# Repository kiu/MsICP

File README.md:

# MsICP

Animated LED sign

# License

This project is licensed under the Creative Commons Attribution-NonCommercial 3.0 Unported (CC BY-NC 3.0) license.

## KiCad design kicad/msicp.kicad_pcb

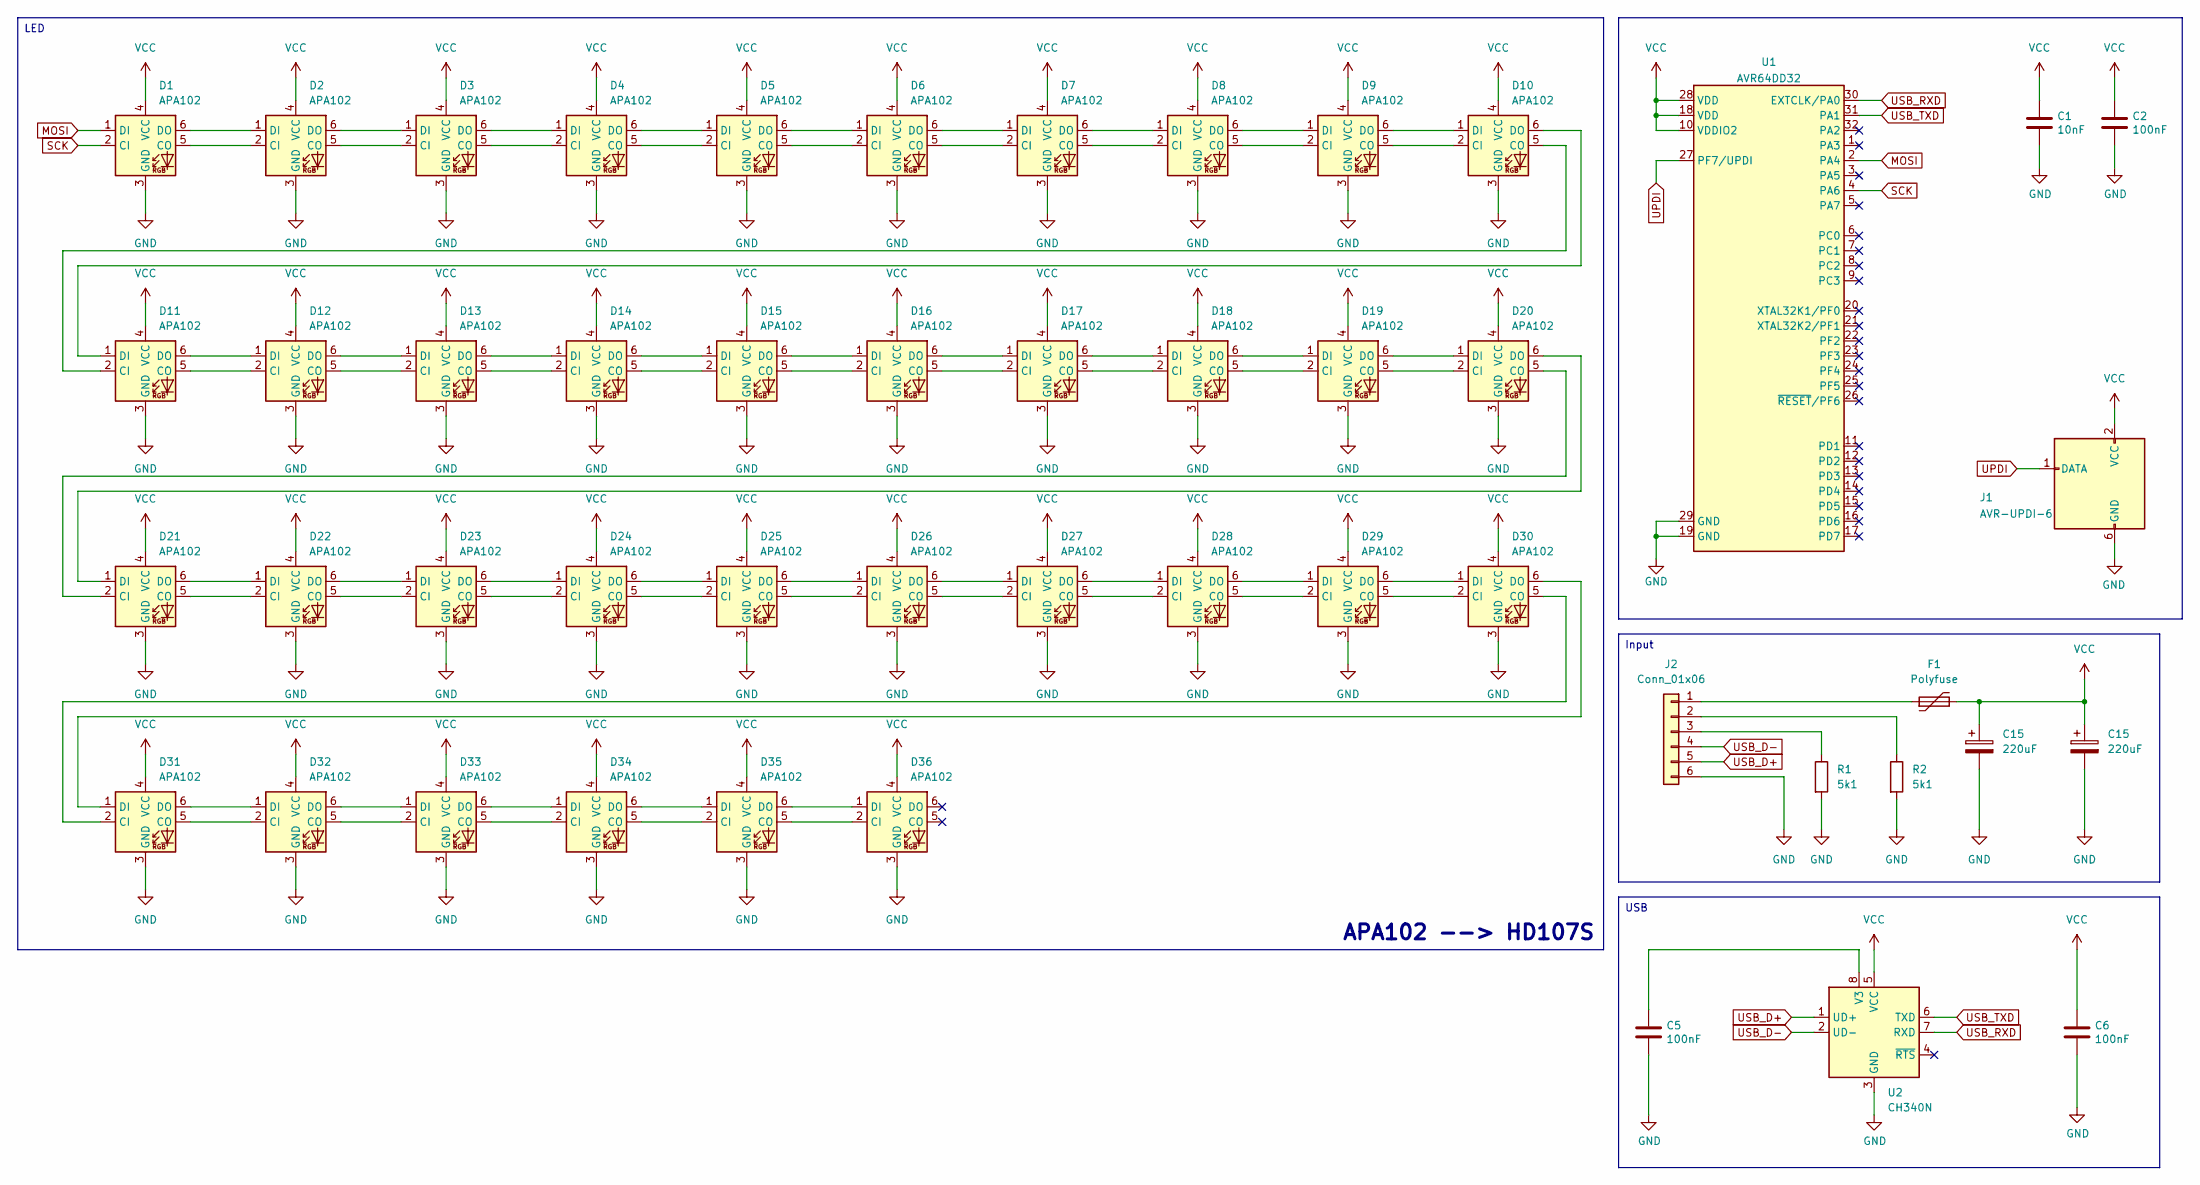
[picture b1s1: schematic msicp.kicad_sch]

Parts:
C1: 10nF; C_0805_2012Metric
C2, C5, C6: 100nF; C_0805_2012Metric
C15: 220uF; CP_EIA-6032-28_Kemet-C; JLC C16133
D1, D2, D3, D4, D5, D6, D7, D8, D9, D10, D11, D12, D13, D14, D15, D16, D17, D18, D19, D20, D21, D22, D23, D24, D25, D26, D27, D28, D29, D30, D31, D32, D33, D34, D35, D36: APA102; LED_RGB_5050-6
F1: Polyfuse; Fuse_0805_2012Metric; JLC C2897461
J1: AVR-UPDI-6; IDC-Header_2x03_P2.54mm_Vertical
J2: Conn_01x06; PinHeader_1x06_P2.54mm_Vertical
R1, R2: 5k1; R_0805_2012Metric
U1: AVR64DD32; TQFP-32_7x7mm_P0.8mm
U2: CH340N; SOP-8_3.9x4.9mm_P1.27mm

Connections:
GND: C1.2, C2.2, C5.2, C6.2, D1.3 (GND), D2.3 (GND), D3.3 (GND), D4.3 (GND), D5.3 (GND), D6.3 (GND), D7.3 (GND), D8.3 (GND), D9.3 (GND), D10.3 (GND), D11.3 (GND), D12.3 (GND), D13.3 (GND), D14.3 (GND), D15.3 (GND), D16.3 (GND), D17.3 (GND), D18.3 (GND), D19.3 (GND), D20.3 (GND), D21.3 (GND), D22.3 (GND), D23.3 (GND), D24.3 (GND), D25.3 (GND), D26.3 (GND), D27.3 (GND), D28.3 (GND), D29.3 (GND), D30.3 (GND), D31.3 (GND), D32.3 (GND), D33.3 (GND), D34.3 (GND), D35.3 (GND), D36.3 (GND), J1.6 (GND), J2.6, R1.2, R2.2, U1.19 (GND), U1.29 (GND), U2.3 (GND); also elsewhere on the board
MOSI: D1.1 (DI), U1.2 (PA4)
unnamed: D1.5 (CO), D2.2 (CI)
unnamed: D1.6 (DO), D2.1 (DI)
unnamed: D2.5 (CO), D3.2 (CI)
unnamed: D2.6 (DO), D3.1 (DI)
unnamed: D3.5 (CO), D4.2 (CI)
unnamed: D3.6 (DO), D4.1 (DI)
unnamed: D4.5 (CO), D5.2 (CI)
unnamed: D4.6 (DO), D5.1 (DI)
unnamed: D5.5 (CO), D6.2 (CI)
unnamed: D5.6 (DO), D6.1 (DI)
unnamed: D6.5 (CO), D7.2 (CI)
unnamed: D6.6 (DO), D7.1 (DI)
unnamed: D7.5 (CO), D8.2 (CI)
unnamed: D7.6 (DO), D8.1 (DI)
unnamed: D8.5 (CO), D9.2 (CI)
unnamed: D8.6 (DO), D9.1 (DI)
unnamed: D9.5 (CO), D10.2 (CI)
unnamed: D10.5 (CO), D11.2 (CI)
unnamed: D9.6 (DO), D10.1 (DI)
unnamed: D10.6 (DO), D11.1 (DI)
unnamed: D11.5 (CO), D12.2 (CI)
unnamed: D11.6 (DO), D12.1 (DI)
unnamed: D12.5 (CO), D13.2 (CI)
unnamed: D12.6 (DO), D13.1 (DI)
unnamed: D13.5 (CO), D14.2 (CI)
unnamed: D13.6 (DO), D14.1 (DI)
unnamed: D14.5 (CO), D15.2 (CI)
unnamed: D14.6 (DO), D15.1 (DI)
unnamed: D15.5 (CO), D16.2 (CI)
unnamed: D15.6 (DO), D16.1 (DI)
unnamed: D16.5 (CO), D17.2 (CI)
unnamed: D16.6 (DO), D17.1 (DI)
unnamed: D17.5 (CO), D18.2 (CI)
unnamed: D17.6 (DO), D18.1 (DI)
unnamed: D18.5 (CO), D19.2 (CI)
unnamed: D18.6 (DO), D19.1 (DI)
unnamed: D19.5 (CO), D20.2 (CI)
unnamed: D19.6 (DO), D20.1 (DI)
unnamed: D20.5 (CO), D21.2 (CI)
unnamed: D20.6 (DO), D21.1 (DI)
unnamed: D21.5 (CO), D22.2 (CI)
unnamed: D21.6 (DO), D22.1 (DI)
unnamed: D22.5 (CO), D23.2 (CI)
unnamed: D22.6 (DO), D23.1 (DI)
unnamed: D23.5 (CO), D24.2 (CI)
unnamed: D23.6 (DO), D24.1 (DI)
unnamed: D24.5 (CO), D25.2 (CI)
unnamed: D24.6 (DO), D25.1 (DI)
unnamed: D25.5 (CO), D26.2 (CI)
unnamed: D25.6 (DO), D26.1 (DI)
unnamed: D26.5 (CO), D27.2 (CI)
unnamed: D26.6 (DO), D27.1 (DI)
unnamed: D27.5 (CO), D28.2 (CI)
unnamed: D27.6 (DO), D28.1 (DI)
unnamed: D28.5 (CO), D29.2 (CI)
unnamed: D28.6 (DO), D29.1 (DI)
unnamed: D29.5 (CO), D30.2 (CI)
unnamed: D29.6 (DO), D30.1 (DI)
unnamed: D30.5 (CO), D31.2 (CI)
unnamed: D30.6 (DO), D31.1 (DI)
unnamed: D31.5 (CO), D32.2 (CI)
unnamed: D31.6 (DO), D32.1 (DI)
unnamed: D32.5 (CO), D33.2 (CI)
unnamed: D32.6 (DO), D33.1 (DI)
unnamed: D33.5 (CO), D34.2 (CI)
unnamed: D33.6 (DO), D34.1 (DI)
unnamed: D34.5 (CO), D35.2 (CI)
unnamed: D34.6 (DO), D35.1 (DI)
unnamed: D35.5 (CO), D36.2 (CI)
unnamed: D35.6 (DO), D36.1 (DI)
unnamed: F1.1, J2.1
unnamed: J2.2, R2.1
unnamed: J2.3, R1.1
unnamed: C5.1, U2.8 (V3)
SCK: D1.2 (CI), U1.4 (PA6)
UPDI: J1.1 (DATA), U1.27 (PF7/UPDI)
USB_D+: J2.5, U2.1 (UD+)
USB_D-: J2.4, U2.2 (UD-)
USB_RXD: U1.30 (EXTCLK/PA0), U2.7 (RXD)
USB_TXD: U1.31 (PA1), U2.6 (TXD)
VCC: C1.1, C2.1, C6.1, D1.4 (VCC), D2.4 (VCC), D3.4 (VCC), D4.4 (VCC), D5.4 (VCC), D6.4 (VCC), D7.4 (VCC), D8.4 (VCC), D9.4 (VCC), D10.4 (VCC), D11.4 (VCC), D12.4 (VCC), D13.4 (VCC), D14.4 (VCC), D15.4 (VCC), D16.4 (VCC), D17.4 (VCC), D18.4 (VCC), D19.4 (VCC), D20.4 (VCC), D21.4 (VCC), D22.4 (VCC), D23.4 (VCC), D24.4 (VCC), D25.4 (VCC), D26.4 (VCC), D27.4 (VCC), D28.4 (VCC), D29.4 (VCC), D30.4 (VCC), D31.4 (VCC), D32.4 (VCC), D33.4 (VCC), D34.4 (VCC), D35.4 (VCC), D36.4 (VCC), F1.2, J1.2 (VCC), U1.10 (VDDIO2), U1.18 (VDD), U1.28 (VDD), U2.5 (VCC); also elsewhere on the board

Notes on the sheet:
Input
USB
LED
APA102 --> HD107S

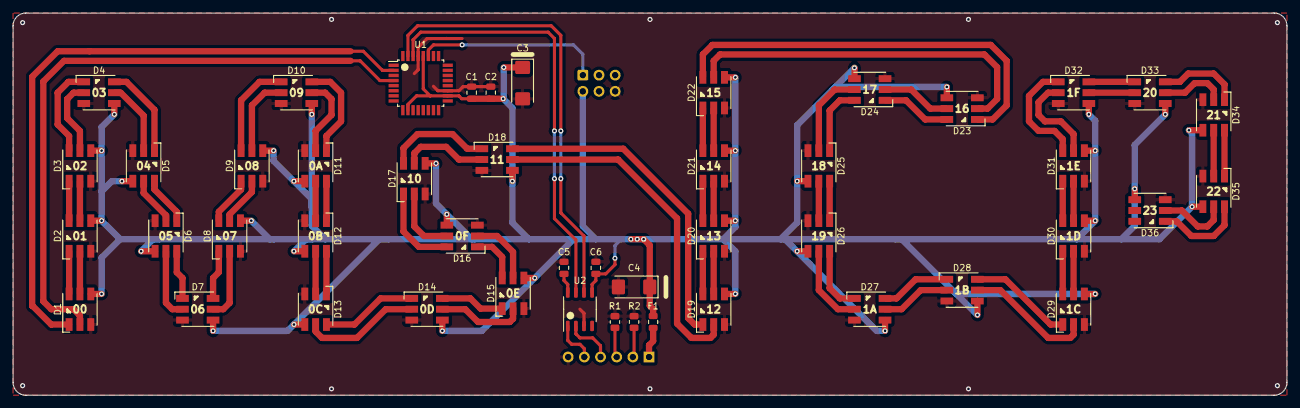
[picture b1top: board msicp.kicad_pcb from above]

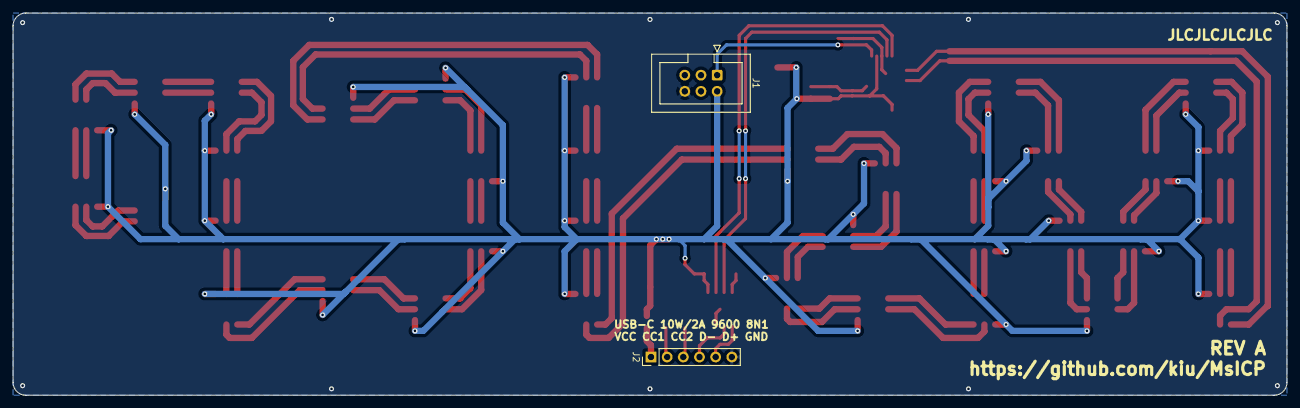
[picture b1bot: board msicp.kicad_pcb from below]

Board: 2 copper layers, 200.0 x 60.0 mm, 49 parts (2 on the bottom side), 83 nets.

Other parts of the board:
C3, C4: 220uF; CP_EIA-6032-28_Kemet-C

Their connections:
GND: C3.2, C4.2; also elsewhere on the board
VCC: C3.1, C4.1; also elsewhere on the board

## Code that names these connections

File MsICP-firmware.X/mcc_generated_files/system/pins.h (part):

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
/**
 * @ingroup  pinsdriver
 * @brief Default Interrupt Handler for IO_PA1 pin. 
 *        This is a predefined interrupt handler to be used together with the IO_PA1_SetInterruptHandler() method.
 *        This handler is called every time the IO_PA1 ISR is executed. 
 * @pre PIN_MANAGER_Initialize() has been called at least once
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
/**
 * @ingroup  pinsdriver
 * @brief Interrupt Handler Setter for IO_PA1 pin input-sense-config functionality.
 *        Allows selecting an interrupt handler for IO_PA1 at application runtime
 * @pre PIN_MANAGER_Initialize() has been called at least once
 * @param InterruptHandler function pointer.
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
/**
 * @ingroup  pinsdriver
 * @brief Default Interrupt Handler for IO_PA0 pin. 
 *        This is a predefined interrupt handler to be used together with the IO_PA0_SetInterruptHandler() method.
 *        This handler is called every time the IO_PA0 ISR is executed. 
 * @pre PIN_MANAGER_Initialize() has been called at least once
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
/**
 * @ingroup  pinsdriver
 * @brief Interrupt Handler Setter for IO_PA0 pin input-sense-config functionality.
 *        Allows selecting an interrupt handler for IO_PA0 at application runtime
 * @pre PIN_MANAGER_Initialize() has been called at least once
 * @param InterruptHandler function pointer.
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
/**
 * @ingroup  pinsdriver
 * @brief Default Interrupt Handler for IO_PA4 pin. 
 *        This is a predefined interrupt handler to be used together with the IO_PA4_SetInterruptHandler() method.
 *        This handler is called every time the IO_PA4 ISR is executed. 
 * @pre PIN_MANAGER_Initialize() has been called at least once
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
/**
 * @ingroup  pinsdriver
 * @brief Interrupt Handler Setter for IO_PA4 pin input-sense-config functionality.
 *        Allows selecting an interrupt handler for IO_PA4 at application runtime
 * @pre PIN_MANAGER_Initialize() has been called at least once
 * @param InterruptHandler function pointer.
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
/**
 * @ingroup  pinsdriver
 * @brief Default Interrupt Handler for IO_PA6 pin. 
 *        This is a predefined interrupt handler to be used together with the IO_PA6_SetInterruptHandler() method.
 *        This handler is called every time the IO_PA6 ISR is executed. 
 * @pre PIN_MANAGER_Initialize() has been called at least once
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
/**
 * @ingroup  pinsdriver
 * @brief Interrupt Handler Setter for IO_PA6 pin input-sense-config functionality.
 *        Allows selecting an interrupt handler for IO_PA6 at application runtime
 * @pre PIN_MANAGER_Initialize() has been called at least once
 * @param InterruptHandler function pointer.
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

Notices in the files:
MsICP-firmware.X/mcc_generated_files/system/pins.h:
© [2024] Microchip Technology Inc. and its subsidiaries.
